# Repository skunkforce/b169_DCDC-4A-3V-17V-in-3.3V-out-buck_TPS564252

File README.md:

# edgy_board number b169
This design is part of the [edgy board project](https://github.com/skunkforce/edgy_boards).

# getting started
This repository uses submodules. After cloning use the command 

```$ git submodule update --init --recursive```

to pull the submodules before opening the project with kicad. 

# Tests
Tests can be found in [TESTS.md](TESTS.md)

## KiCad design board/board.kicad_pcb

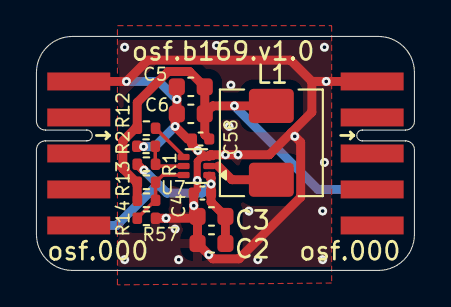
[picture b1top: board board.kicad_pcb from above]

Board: 2 copper layers, 21.0 x 13.0 mm, 17 parts (1 on the bottom side), 7 nets.

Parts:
C2, C3: 10uF; C_0603_1608Metric
C4, C58: 100nF; C_0402_1005Metric
C5, C6: 22uF; C_0603_1608Metric
J1: 000_3.3v_5v; on_edge_2x05_device
J2: 000_3.3v_5v; on_edge_2x05_host
L1: MWSA0503S-3R3MT; L_Sunlord_MWSA0503S
LOGO1: Logo_Open_Hardware_Small; OSHW-Symbol_6.7x6mm_SilkScreen
R1: 47k; R_0402_1005Metric
R2: 12k; R_0402_1005Metric
R12, R57: 10k; R_0402_1005Metric
R13: 49.9k; R_0402_1005Metric
R14: 510k; R_0402_1005Metric
U7: TPS564257DRLR; SOT-563

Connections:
/buck/3.3V: C5.1, C6.1, C58.1, J2.9 (3.3V), L1.2, R12.2, R13.2, R14.2
/buck/EN: R1.1, R2.2, U7.5 (EN)
/buck/PG: R12.1, U7.4 (PG)
/buck/Vin: C2.1, C3.1, C4.1, J1.10 (5V), R1.2, U7.1 (VIN)
/buck/sw: L1.1, U7.2 (SW)
GND: C2.2, C3.2, C4.2, C5.2, C6.2, C58.2, J1.1 (GND), J2.1 (GND), R2.1, R57.1, U7.3 (GND)
unnamed: R13.1, R14.1, R57.2, U7.6 (FB)

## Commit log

2025-04-30 initial
